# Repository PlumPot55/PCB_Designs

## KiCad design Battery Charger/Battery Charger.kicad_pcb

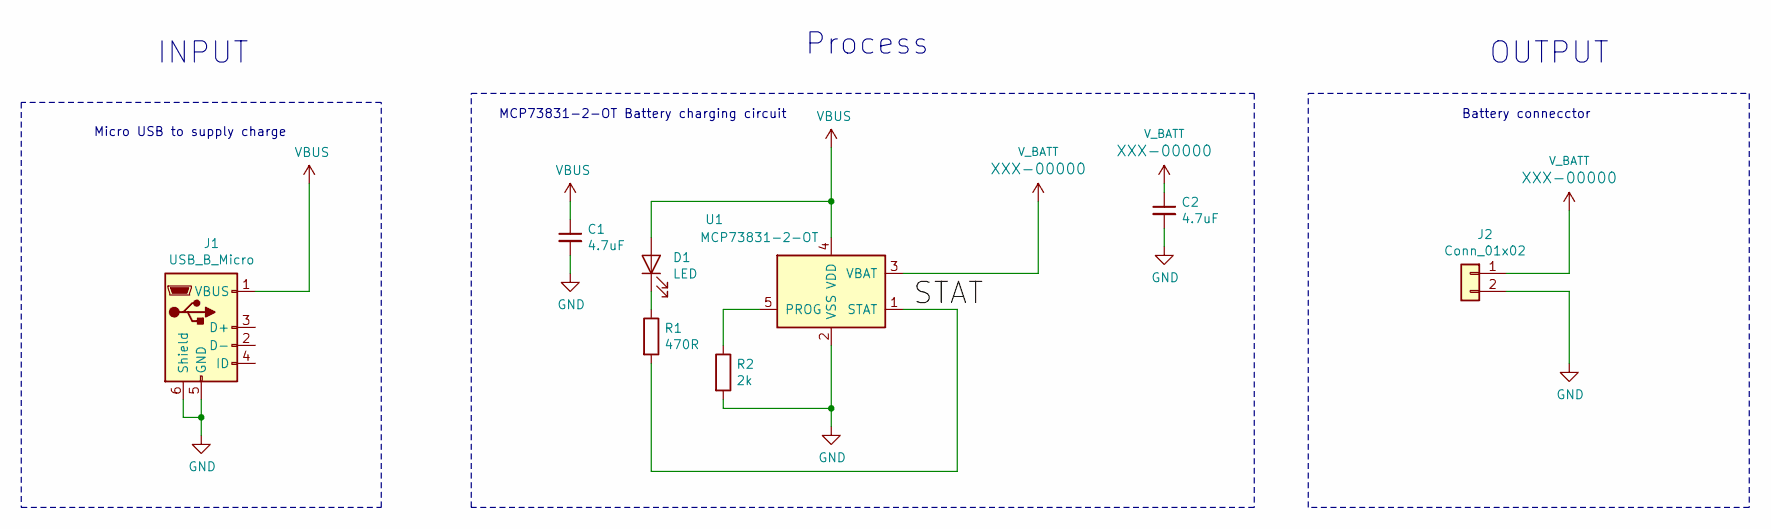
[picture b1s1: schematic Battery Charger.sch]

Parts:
C1, C2: 4.7uF; C_1206_3216Metric_Pad1.42x1.75mm_HandSolder
D1: LED; LED_1206_3216Metric_Pad1.42x1.75mm_HandSolder
J1: USB_B_Micro; USB_Micro-B_Molex-105017-0001
J2: Conn_01x02; JST_GH_SM02B-GHS-TB_1x02-1MP_P1.25mm_Horizontal
R1: 470R; R_1206_3216Metric_Pad1.42x1.75mm_HandSolder
R2: 2k; R_1206_3216Metric_Pad1.42x1.75mm_HandSolder
U1: MCP73831-2-OT; SOT-23-5

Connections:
/STAT: R1.2, U1.1 (STAT)
GND: C1.2, C2.2, J1.5 (GND), J1.6 (Shield), J2.2, R2.2, U1.2 (VSS)
unnamed: D1.1 (K), R1.1
unnamed: R2.1, U1.5 (PROG)
VBUS: C1.1, D1.2 (A), J1.1 (VBUS), U1.4 (VDD)
V_BATT: C2.1, J2.1, U1.3 (VBAT)

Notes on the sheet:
Micro USB to supply charge
MCP73831-2-OT Battery charging circuit
Battery connecctor
INPUT
Process
OUTPUT

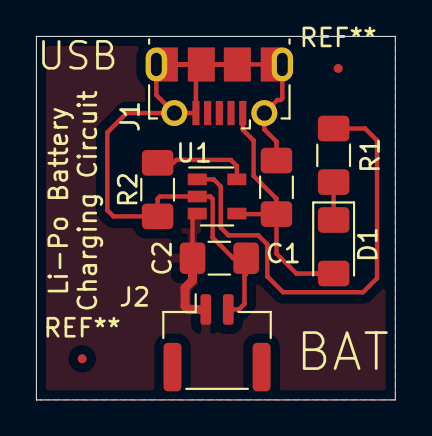
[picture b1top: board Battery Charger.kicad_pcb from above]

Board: 2 copper layers, 19.9 x 20.2 mm, 8 parts (0 on the bottom side), 6 nets.

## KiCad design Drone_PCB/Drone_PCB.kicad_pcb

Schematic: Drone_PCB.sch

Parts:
C1, C2, C8, C10: 10uF; C_0603_1608Metric_Pad1.05x0.95mm_HandSolder
C3, C9, C11, C12: 0.1uF; C_0603_1608Metric_Pad1.05x0.95mm_HandSolder
C7: 4.7uF; C_0603_1608Metric_Pad1.05x0.95mm_HandSolder
C13: 2.2nF; C_0603_1608Metric_Pad1.05x0.95mm_HandSolder
D2, D3, D4, D5: D_Schottky
J1, J2, J3, J4: Conn_01x02
J5: USB_B_Mini; USB_Micro-B_Molex-105017-0001
J6, J7, J8: Conn_01x05; PinHeader_1x05_P2.54mm_Vertical
Q1, Q2: TRANS_NPN-MMBT2222AL; SOT23-3
R3, R4, R12, R13, R14, R15: 10K; R_0603_1608Metric_Pad1.05x0.95mm_HandSolder
R5, R6, R7: 100R; R_0603_1608Metric_Pad1.05x0.95mm_HandSolder
R8, R9: 100K; R_0603_1608Metric_Pad1.05x0.95mm_HandSolder
R10, R11: 2k2; R_0603_1608Metric_Pad1.05x0.95mm_HandSolder
R16, R17: 0R; R_0603_1608Metric_Pad1.05x0.95mm_HandSolder
S1: MOMENTARY-SWITCH-SPST-2-SMD-4.6X2.8MM; TACTILE_SWITCH_SMD_4.6X2.8MM
U1: ESP32-WROOM-32
U2: CP2104; QFN-24-1EP_4x4mm_P0.5mm_EP2.6x2.6mm
U3, U5, U8, U9: SI2302-TP; SOT-23
U4: MIC5219-3.3YMM; MSOP-8_3x3mm_P0.65mm
U6: MPU-6050; InvenSense_QFN-24_4x4mm_P0.5mm

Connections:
+3V3: C2.1, C3.1, C8.1, C9.1, C10.1, C11.1, R7.1, R10.1, R11.2, R16.2, U1.2 (VDD), U2.5 (VIO), U2.6 (VDD), U2.7 (REGIN), U4.3 (OUT), U6.8 (VDDIO), U6.13 (VDD)
/AD0: R16.1, R17.2, U6.9 (AD0)
/AUX_SCL: U6.7 (AUX_SCL)
/AUX_SDA: U6.6 (AUX_SDA)
/D+: J5.3 (D+), U2.3 (D+)
/D-: J5.2 (D-), U2.4 (D-)
/DTR: Q1.2 (E), R4.1, U2.23 (DTR)
/GPIO0: Q1.3 (C), U1.25 (IO0)
/INT: U1.6 (IO34), U6.12 (INT)
/IO25: U1.10 (IO25)
/IO26: U1.11 (IO26)
/IO27: U1.12 (IO27)
/IO32: U1.8 (IO32)
/IO33: U1.9 (IO33)
/M1-: D2.2 (A), J1.2, U3.3
/M1_PWM: R12.1, U1.13 (IO14), U3.1
/M2-: D3.2 (A), J2.2, U5.3
/M2_PWM: R13.1, U1.27 (IO16), U5.1
/M3-: D4.2 (A), J3.2, U8.3
/M3_PWM: R14.1, U1.14 (IO12), U8.1
/M4-: D5.2 (A), J4.2, U9.3
/M4_PWM: R15.1, U1.30 (IO18), U9.1
/RESET: Q2.3 (C), R7.2, S1.3, S1.4, U1.3 (EN)
/RTS: Q2.2 (E), R3.1, U2.19 (RTS)
/RX_CP2104: R6.1, U2.20 (RXD)
/RX_ESP32: R5.2, U1.34 (RXD0/IO3)
/SCK: U1.20 (SCK/CLK)
/SCL: R10.2, U1.36 (IO22), U6.23 (SCL)
/SCS: U1.19 (SCS/CMD)
/SDA: R11.1, U1.33 (IO21), U6.24 (SDA)
/SDI: U1.22 (SDI/SD1)
/SDO: U1.21 (SDO/SD0)
/TX_CP2104: R5.1, U2.21 (TXD)
/TX_ESP32: R6.2, U1.35 (TXD0/IO1)
/V_BAT_Measure: R8.2, R9.1, U1.7 (IO35)
GND: C1.2, C2.2, C3.2, C7.2, C8.2, C9.2, C10.2, C11.2, C12.2, C13.2, J5.5 (GND), J5.6 (Shield), R9.2, R12.2, R13.2, R14.2, R15.2, R17.1, S1.1, S1.2, U1.1 (GND), U1.15 (GND), U1.38 (GND), U1.39 (GND), U2.2 (GND), U2.25 (PAD), U3.2, U4.5 (GND), U4.6 (GND), U4.7 (GND), U4.8 (GND), U5.2, U6.1 (CLKIN), U6.11 (FSYNC), U6.18 (GND), U8.2, U9.2; also elsewhere on the board
unnamed: C7.1, U2.16 (VPP)
unnamed: C12.1, U6.10 (REGOUT)
unnamed: C13.1, U6.20 (CPOUT)
unnamed: Q1.1 (B), R3.2
unnamed: Q2.1 (B), R4.2
VBUS: J5.1 (VBUS), U2.8 (VBUS)
V_BATT: C1.1, D2.1 (K), D3.1 (K), D4.1 (K), D5.1 (K), J1.1, J2.1, J3.1, J4.1, R8.1, U4.1 (EN), U4.2 (IN); also elsewhere on the board

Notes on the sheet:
ESP32
CP2104 USB IC
USB
Accelerometer
3V3 Voltage regulator
Motor connectors
MOSFETS motor Drivers
DO NOT POPULATE
Extra Development Signals

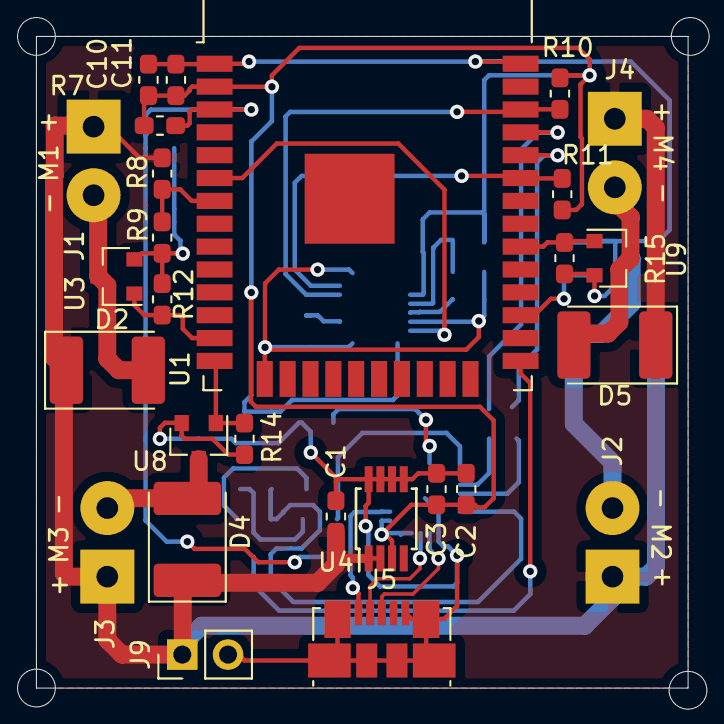
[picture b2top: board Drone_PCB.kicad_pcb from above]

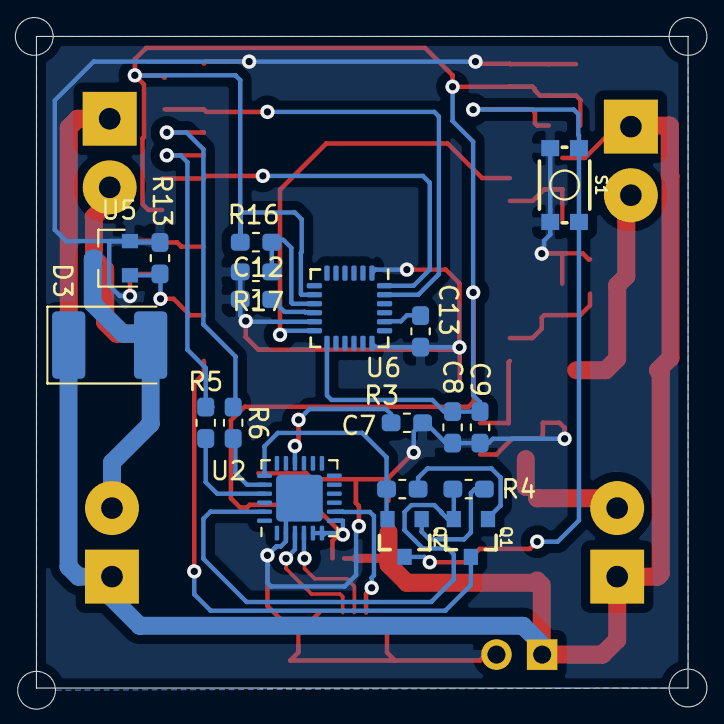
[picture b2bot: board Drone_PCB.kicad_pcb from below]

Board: 2 copper layers, 36.2 x 36.2 mm, 46 parts (19 on the bottom side), 32 nets.

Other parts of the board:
J9: Conn_01x02; PinHeader_1x02_P2.54mm_Vertical

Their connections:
GND: J9.2; also elsewhere on the board
V_BATT: J9.1; also elsewhere on the board

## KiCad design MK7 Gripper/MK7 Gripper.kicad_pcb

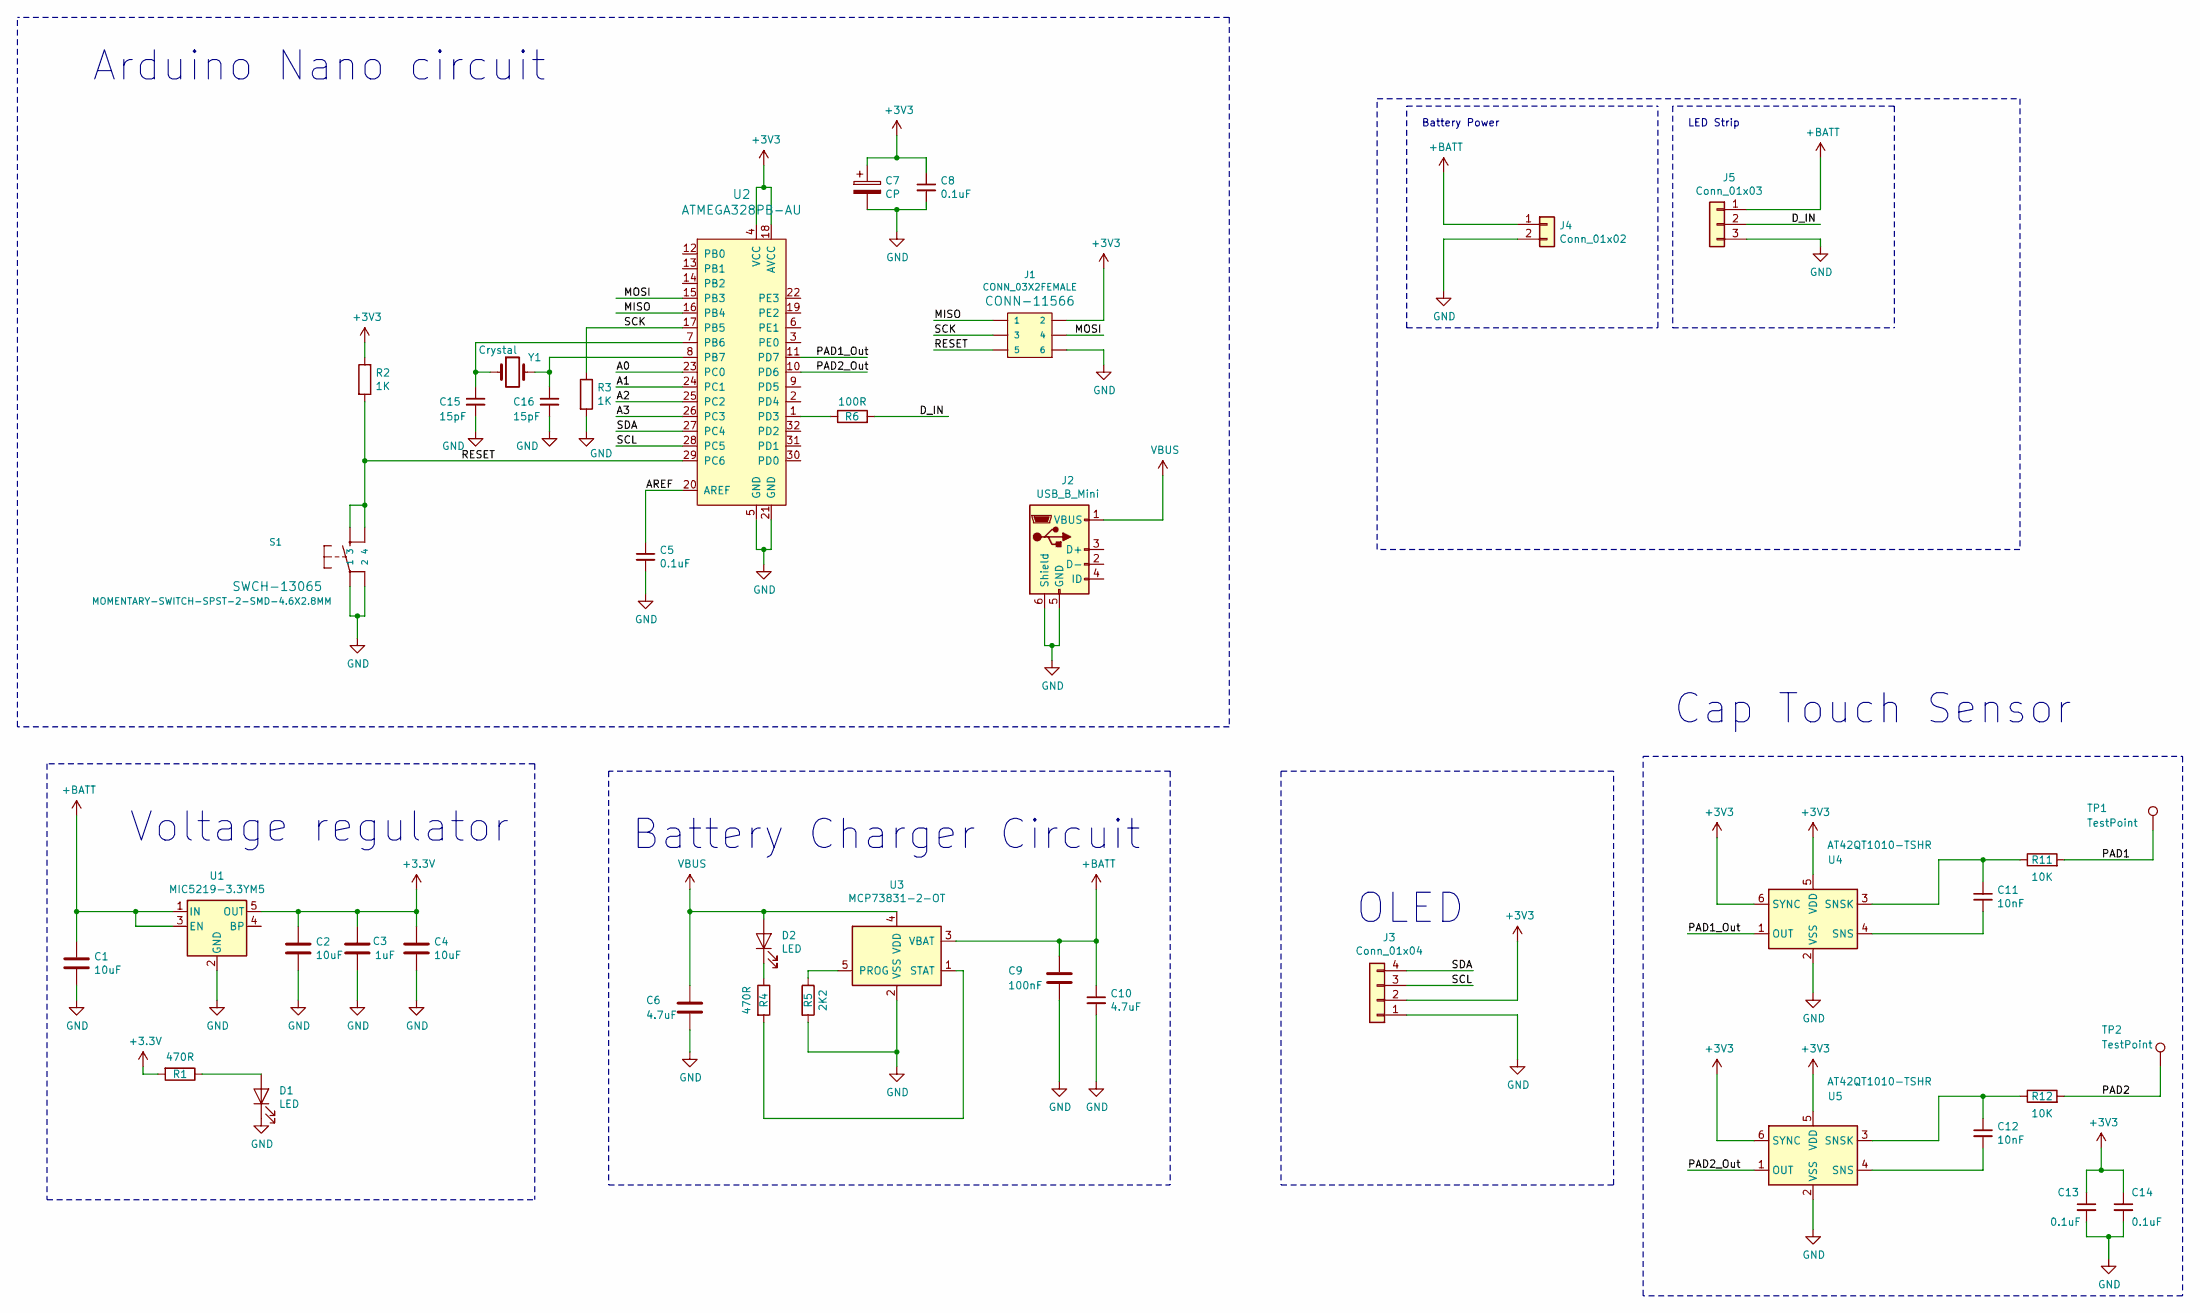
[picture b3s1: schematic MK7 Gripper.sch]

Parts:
C1, C2, C4: 10uF; C_0603_1608Metric_Pad1.05x0.95mm_HandSolder
C3: 1uF; C_0603_1608Metric_Pad1.05x0.95mm_HandSolder
C5, C8, C13, C14: 0.1uF; C_0603_1608Metric_Pad1.05x0.95mm_HandSolder
C6, C10: 4.7uF; C_0603_1608Metric_Pad1.05x0.95mm_HandSolder
C7: CP; C_0603_1608Metric_Pad1.05x0.95mm_HandSolder
C9: 100nF; C_0603_1608Metric_Pad1.05x0.95mm_HandSolder
C11, C12: 10nF; C_0603_1608Metric_Pad1.05x0.95mm_HandSolder
C15, C16: 15pF; C_0603_1608Metric_Pad1.05x0.95mm_HandSolder
D1, D2: LED; LED_1206_3216Metric
J1: CONN_03X2FEMALE; PinHeader_2x03_P2.54mm_Vertical
J2: USB_B_Mini; USB_Micro-B_Molex-105017-0001
J3: Conn_01x04; PinSocket_1x04_P2.54mm_Vertical
J4: Conn_01x02; JST_EH_B2B-EH-A_1x02_P2.50mm_Vertical
J5: Conn_01x03
R1, R4: 470R; R_0603_1608Metric_Pad1.05x0.95mm_HandSolder
R2, R3: 1K; R_0603_1608Metric_Pad1.05x0.95mm_HandSolder
R5: 2K2; R_0603_1608Metric_Pad1.05x0.95mm_HandSolder
R6: 100R; R_0603_1608Metric_Pad1.05x0.95mm_HandSolder
R11, R12: 10K; R_0603_1608Metric_Pad1.05x0.95mm_HandSolder
S1: MOMENTARY-SWITCH-SPST-2-SMD-4.6X2.8MM; SW_PUSH_6mm_H4.3mm
TP1, TP2: TestPoint
U1: MIC5219-3.3YM5; SOT-23-5
U2: ATMEGA328PB-AU; TQFP-32_7x7mm; MPN ATMEGA328PB-AU; Digi-Key_PN ATMEGA328PB-AU-ND
U3: MCP73831-2-OT; SOT-23-5
U4, U5: AT42QT1010-TSHR; SOT-23-6
Y1: Crystal; Resonator-2Pin_W10.0mm_H5.0mm

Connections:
+BATT: C1.1, C9.1, C10.1, J4.1, J5.1, U1.1 (IN), U1.3 (EN), U3.3 (VBAT)
/A0: U2.23 (PC0)
/A1: U2.24 (PC1)
/A2: U2.25 (PC2)
/A3: U2.26 (PC3)
/AREF: C5.1, U2.20 (AREF)
/D_IN: J5.2, R6.2
/MISO: J1.1, U2.16 (PB4)
/MOSI: J1.4, U2.15 (PB3)
/PAD1: R11.2, TP1.1
/PAD1_Out: U2.11 (PD7), U4.1 (OUT)
/PAD2: R12.2, TP2.1
/PAD2_Out: U2.10 (PD6), U5.1 (OUT)
/RESET: J1.5, R2.2, S1.3, S1.4, U2.29 (PC6)
/SCK: J1.3, R3.1, U2.17 (PB5)
/SCL: J3.3, U2.28 (PC5)
/SDA: J3.4, U2.27 (PC4)
GND: C1.2, C2.2, C3.2, C4.2, C5.2, C6.2, C7.2, C8.2, C9.2, C10.2, C13.2, C14.2, C15.2, C16.2, D1.1 (K), J1.6, J2.5 (GND), J2.6 (Shield), J3.1, J4.2, J5.3, R3.2, R5.2, S1.1, S1.2, U1.2 (GND), U2.5 (GND), U2.21 (GND), U3.2 (VSS), U4.2 (VSS), U5.2 (VSS)
unnamed: C11.1, R11.1, U4.3 (SNSK)
unnamed: C11.2, U4.4 (SNS)
unnamed: C12.1, R12.1, U5.3 (SNSK)
unnamed: C12.2, U5.4 (SNS)
unnamed: C15.1, U2.7 (PB6), Y1.1
unnamed: C16.1, U2.8 (PB7), Y1.2
unnamed: D1.2 (A), R1.1
unnamed: D2.1 (K), R4.1
unnamed: R4.2, U3.1 (STAT)
unnamed: R5.1, U3.5 (PROG)
unnamed: R6.1, U2.1 (PD3)
VBUS: C6.1, D2.2 (A), J2.1 (VBUS), U3.4 (VDD)

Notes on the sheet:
LED Strip
Battery Power
Arduino Nano circuit
Battery Charger Circuit
Voltage regulator
OLED
Cap Touch Sensor

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
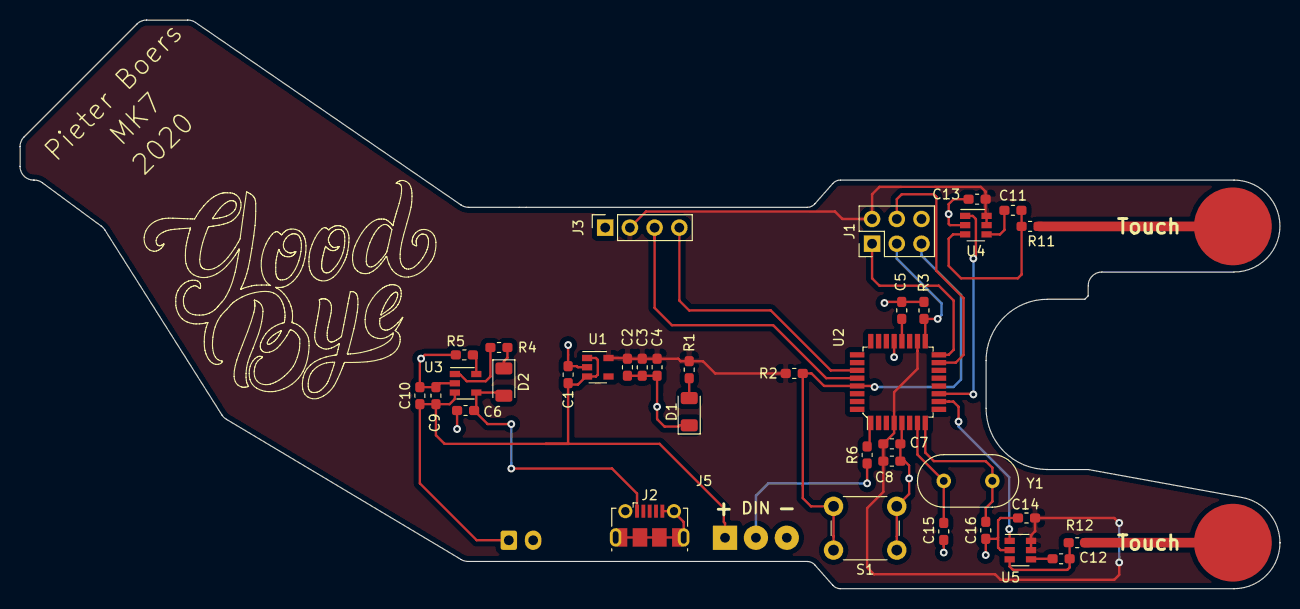
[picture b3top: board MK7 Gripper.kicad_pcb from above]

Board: 2 copper layers, 129.5 x 58.5 mm, 40 parts (1 on the bottom side), 27 nets.

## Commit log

2020-08-04 Robot Gripper
    Robot Gripper Ki-Cad Files we did on Sunday 26th of July 2020 - Check YouTube for details
2020-08-04 Drone Controller
    PCB we started desiging on the 2nd of August 2020
2020-08-19 V2 - With Mosfets
    Removed the H-Bridge added the MOSFETS
2020-08-23 Routing Part 6
    We made the tracks thicker and removed some components
2020-08-23 Routed completed Ready to order I hope
2020-08-31 updated drone and battery charger
2020-09-03 Arduino Code for Gripper
2020-10-19 Updated Latest
2020-11-01 Updated Macro Keybpard
2020-11-22 Updated Macro Keyboard
2021-02-06 Update
    Added
    simple Keyboard
    Removed drone zip
2021-03-13 The Arduino Code for the Keyboard
    Here is the Arduino Code for the Keyboard
2021-03-13 Libraries I needed for the the Keyboard to work
2021-03-14 Library that works with Ws2128B With the Blue Pill
